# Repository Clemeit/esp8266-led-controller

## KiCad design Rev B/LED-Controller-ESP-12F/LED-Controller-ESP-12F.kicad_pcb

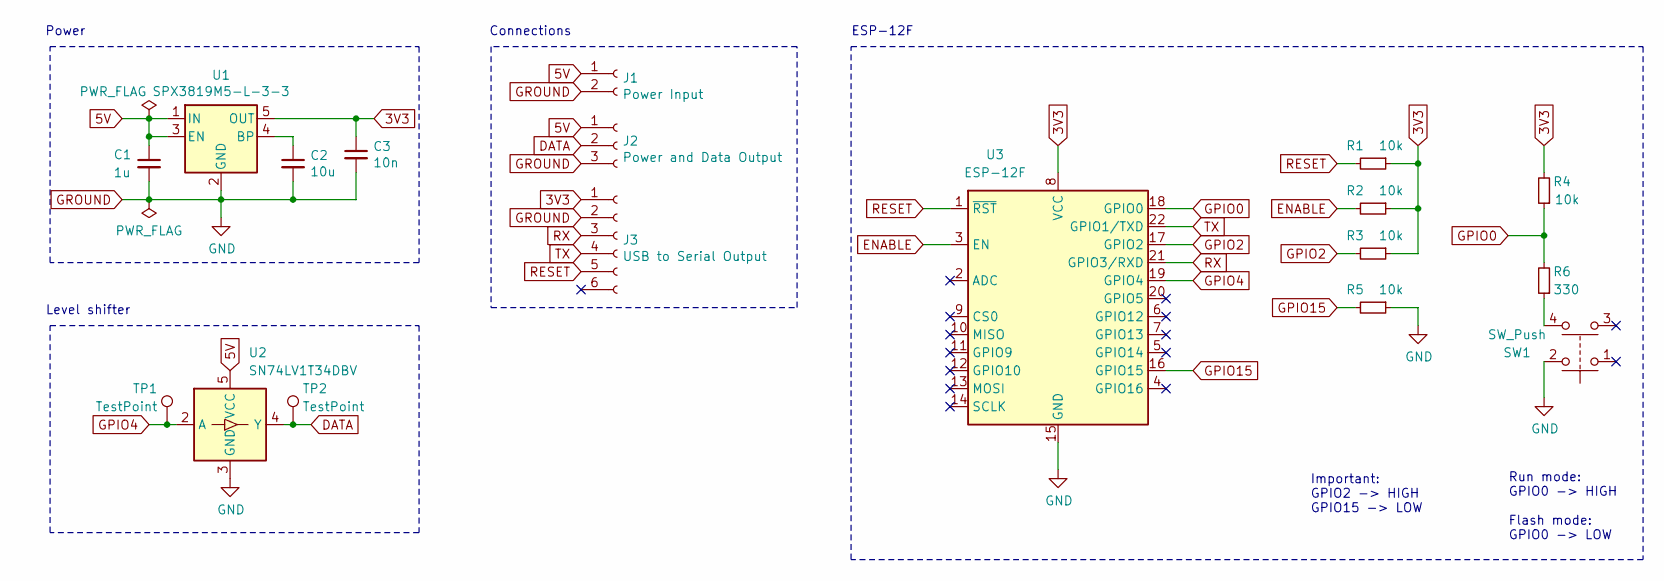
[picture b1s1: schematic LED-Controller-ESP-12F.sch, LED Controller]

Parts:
C1: 1u; C_0805_2012Metric_Pad1.18x1.45mm_HandSolder
C2: 10u; C_0805_2012Metric_Pad1.18x1.45mm_HandSolder
C3: 10n; C_0805_2012Metric_Pad1.18x1.45mm_HandSolder
J1: Power Input; PinHeader_1x02_P2.54mm_Vertical
J2: Power and Data Output; PinHeader_1x03_P2.54mm_Vertical
J3: USB to Serial Output; PinSocket_1x06_P2.54mm_Vertical
R1, R2, R3, R4, R5: 10k; R_0805_2012Metric_Pad1.20x1.40mm_HandSolder
R6: 330; R_0805_2012Metric_Pad1.20x1.40mm_HandSolder
SW1: SW_Push; LL3301FF065QJ
TP1, TP2: TestPoint; TestPoint_THTPad_D2.0mm_Drill1.0mm
U1: SPX3819M5-L-3-3; SOT-23-5
U2: SN74LV1T34DBV; SOT-23-5
U3: ESP-12F; ESP-12E

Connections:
3V3: C3.1, J3.1, R1.1, R2.1, R3.1, R4.2, U1.5 (OUT), U3.8 (VCC)
5V: C1.1, J1.1, J2.1, U1.1 (IN), U1.3 (EN), U2.5 (VCC)
DATA: J2.2, TP2.1, U2.4 (Y)
ENABLE: R2.2, U3.3 (EN)
GPIO0: R4.1, R6.2, U3.18 (GPIO0)
GPIO2: R3.2, U3.17 (GPIO2)
GPIO4: TP1.1, U2.2 (A), U3.19 (GPIO4)
GPIO15: R5.2, U3.16 (GPIO15)
GROUND: C1.2, C2.2, C3.2, J1.2, J2.3, J3.2, R5.1, SW1.2, U1.2 (GND), U2.3 (GND), U3.15 (GND)
unnamed: C2.1, U1.4 (BP)
unnamed: R6.1, SW1.4
RESET: J3.5, R1.2, U3.1 (~RST)
RX: J3.3, U3.21 (GPIO3/RXD)
TX: J3.4, U3.22 (GPIO1/TXD)

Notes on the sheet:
Power
ESP-12F
Important: GPIO2 -> HIGH GPIO15 -> LOW
Run mode: GPIO0 -> HIGH Flash mode: GPIO0 -> LOW
Level shifter
Connections

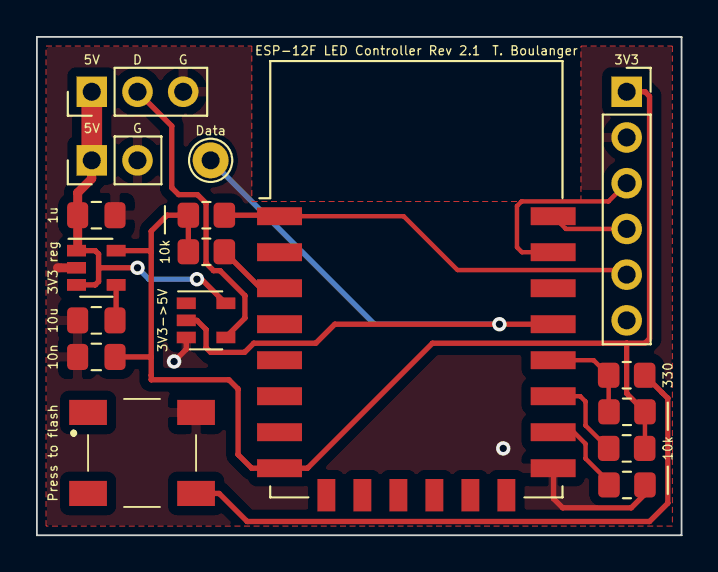
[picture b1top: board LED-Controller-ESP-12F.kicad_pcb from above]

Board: 2 copper layers, 35.8 x 27.7 mm, 17 parts (0 on the bottom side), 14 nets.

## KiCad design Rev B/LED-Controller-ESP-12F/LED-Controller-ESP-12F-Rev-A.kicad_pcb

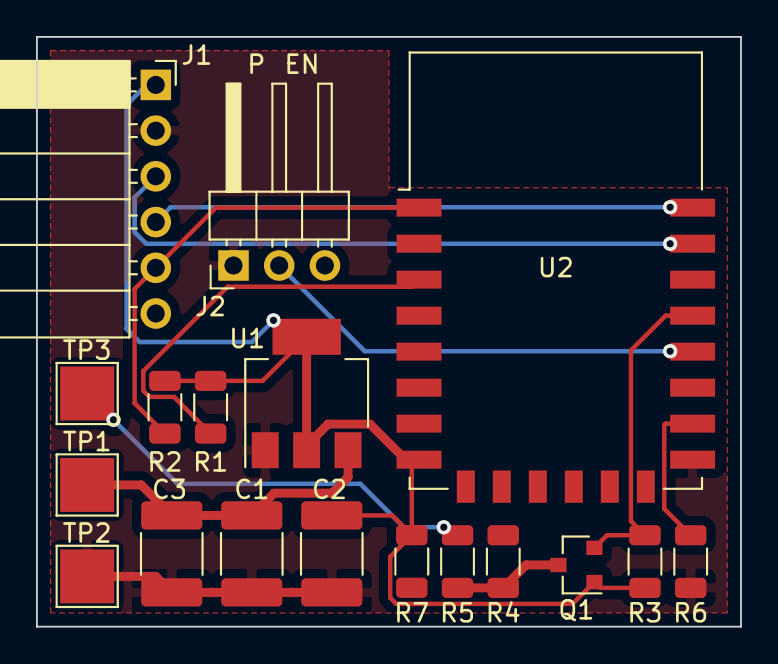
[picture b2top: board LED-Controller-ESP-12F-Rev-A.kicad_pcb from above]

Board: 2 copper layers, 39.1 x 32.8 mm, 18 parts (0 on the bottom side), 13 nets.

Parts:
C1, C2: 10u; C_1812_4532Metric_Pad1.57x3.40mm_HandSolder
C3: 1000u; C_1812_4532Metric_Pad1.57x3.40mm_HandSolder
J1: Conn_01x06_Female; PinSocket_1x06_P2.54mm_Horizontal
J2: Conn_01x06_Female; PinHeader_1x03_P2.54mm_Horizontal
Q1: BSS138; SOT-23
R1, R2, R3, R4, R6, R7: 10k; R_1206_3216Metric
R5: 330; R_1206_3216Metric
TP1: 5V; TestPoint_Pad_3.0x3.0mm
TP2: GND; TestPoint_Pad_3.0x3.0mm
TP3: LED_DATA; TestPoint_Pad_3.0x3.0mm
U1: NCP1117-3.3_SOT223; SOT-223-3_TabPin2
U2: ESP-12F; ESP-12E

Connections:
+5V: C1.1, C3.1, R4.1, TP1.1, U1.3
/RTS: J1.5, R2.2, U2.1
/RX: J1.4, U2.22
/TX: J1.3, U2.21
GND: C1.2, C2.2, C3.2, J1.2, J2.1, R6.2, TP2.1, U1.1, U2.15
unnamed: C2.1, J1.1, Q1.1, R1.1, R2.1, R3.1, R7.1, U1.2, U2.8
unnamed: J2.2, U2.18
unnamed: J2.3, R7.2
unnamed: Q1.2, R3.2, U2.19
unnamed: Q1.3, R4.2, R5.2
unnamed: R1.2, U2.3
unnamed: R5.1, TP3.1
unnamed: R6.1, U2.16

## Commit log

2021-10-27 Created repo
